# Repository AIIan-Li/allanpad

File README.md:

# allanpad

Allanpad is a 9 key macropad with a rotary encoder, and uses KMK firmware.

## Features:
-3d printed case
-EC 11 Rotary encoder
-9 Keys

## CAD Model:
Everything goes together with 4 M3 screws for the case

It has the bottom part where the pcb goes and the top cover for it.

Made in Fusion360

## PCB
The PCB was created in KICAD

Schematic

PCB

## Firmware Overview
The hackpad uses kmk firmware for everything

- the rotary encoder changes volume. press to mute
- The 9 keys are macros that I can change

## BOM:
Everything needed to make the macropad

- 9x Cherry MX Switches
- 9x DSA Keycaps
- 4x M3x5x4 Heatset inserts
- 4x x16mm SHCS Bolts
- 9 1N4148 DO-35 Diodes.
- 1x EC11 Rotary Encoder
- 1x XIAO RP2040
- 1x Case (2 printed parts)

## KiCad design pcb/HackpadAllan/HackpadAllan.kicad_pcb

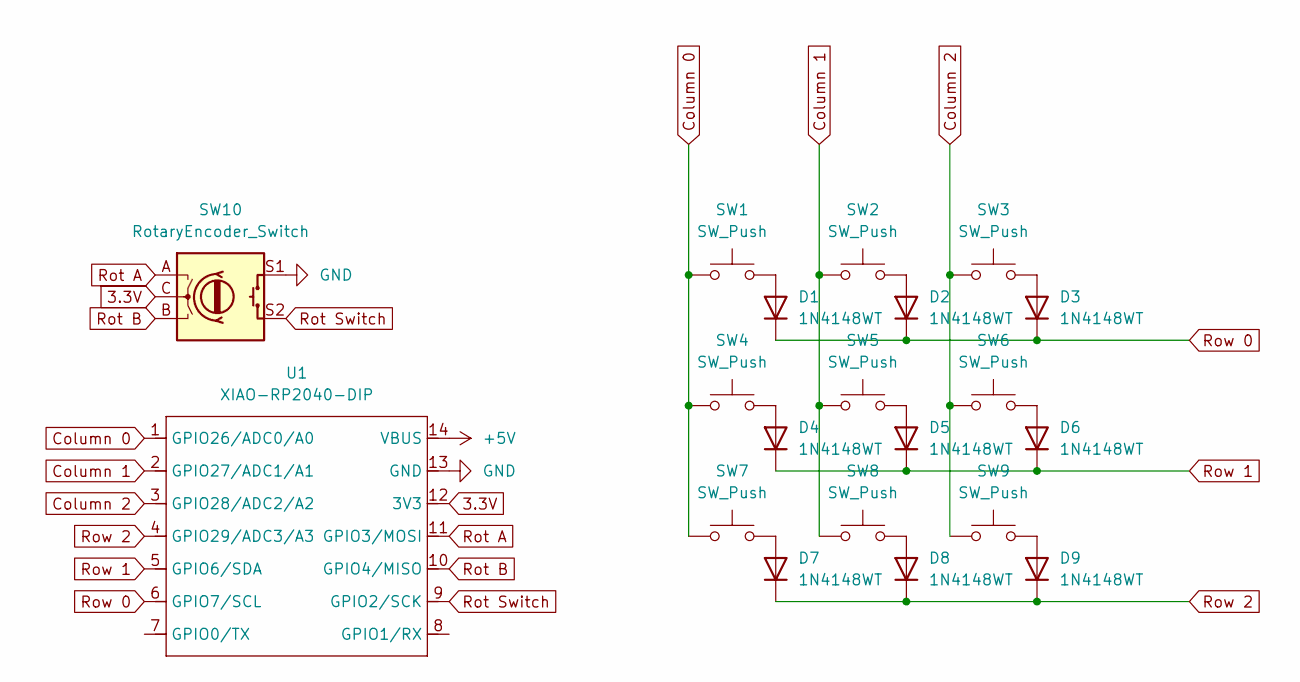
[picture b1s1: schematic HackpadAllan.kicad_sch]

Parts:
D1, D2, D3, D4, D5, D6, D7, D8, D9: 1N4148WT; D_DO-35_SOD27_P2.54mm_Vertical_AnodeUp
SW1, SW2, SW3, SW4, SW5, SW6, SW7, SW8, SW9: SW_Push; SW_Cherry_MX_1.00u_PCB
SW10: RotaryEncoder_Switch; RotaryEncoder_Alps_EC11E-Switch_Vertical_H20mm_MountingHoles
U1: XIAO-RP2040-DIP

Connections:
3.3V: SW10.C, U1.12 (3V3)
+5V: U1.14 (VBUS)
Column 0: SW1.1, SW4.1, SW7.1, U1.1 (GPIO26/ADC0/A0)
Column 1: SW2.1, SW5.1, SW8.1, U1.2 (GPIO27/ADC1/A1)
Column 2: SW3.1, SW6.1, SW9.1, U1.3 (GPIO28/ADC2/A2)
GND: SW10.S1, U1.13 (GND)
unnamed: D1.2 (A), SW1.2
unnamed: D2.2 (A), SW2.2
unnamed: D3.2 (A), SW3.2
unnamed: D4.2 (A), SW4.2
unnamed: D5.2 (A), SW5.2
unnamed: D6.2 (A), SW6.2
unnamed: D7.2 (A), SW7.2
unnamed: D8.2 (A), SW8.2
unnamed: D9.2 (A), SW9.2
Rot A: SW10.A, U1.11 (GPIO3/MOSI)
Rot B: SW10.B, U1.10 (GPIO4/MISO)
Rot Switch: SW10.S2, U1.9 (GPIO2/SCK)
Row 0: D1.1 (K), D2.1 (K), D3.1 (K), U1.6 (GPIO7/SCL)
Row 1: D4.1 (K), D5.1 (K), D6.1 (K), U1.5 (GPIO6/SDA)
Row 2: D7.1 (K), D8.1 (K), D9.1 (K), U1.4 (GPIO29/ADC3/A3)

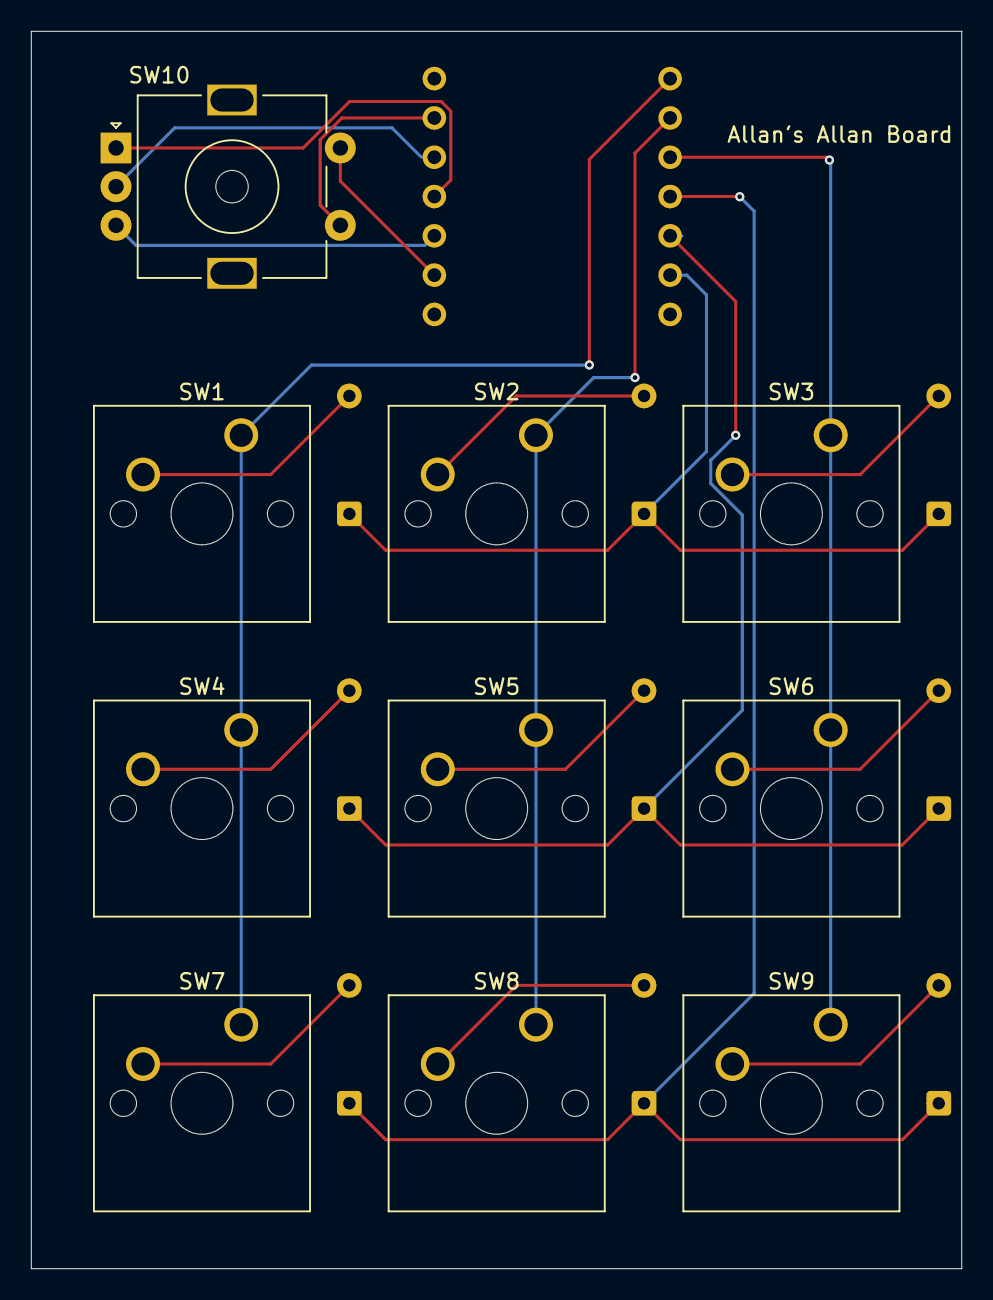
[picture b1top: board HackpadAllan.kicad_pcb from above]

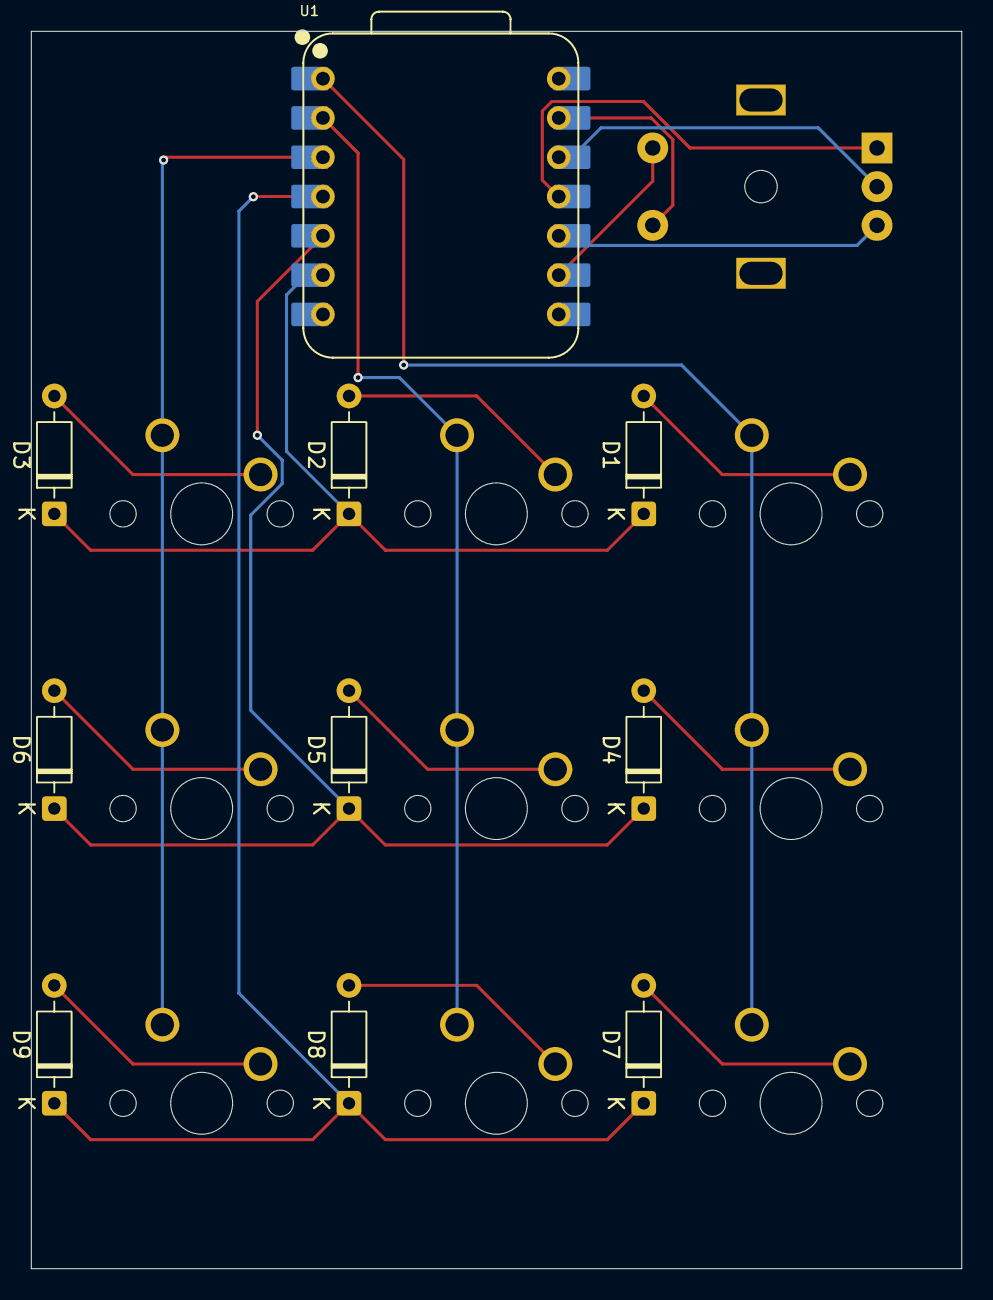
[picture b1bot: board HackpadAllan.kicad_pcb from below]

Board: 2 copper layers, 60.1 x 80.0 mm, 20 parts (10 on the bottom side), 20 nets.

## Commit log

2025-06-01 Completed journaling Schematics and PCB design, will begin adding files later
2025-06-01 journal save
2025-06-02 added all files to the commit, completed README
2025-06-04 fixed pcb, added to journal
2025-06-07 idek tbh finished everysthing so hopefully this doesn't mess anything up
2025-08-11 finish
